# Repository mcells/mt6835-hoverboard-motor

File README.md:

# mt6835-hoverboard-motor
MT6835 Breakout board, eg. for mounting inside Hoverboard motors

| Front | Back |
| ----- | ---- | 
|  |  |

## Features
- MT6835 Encoder
- 25x25mm diagonal M3 mounting holes that are removable by breakaway sections
- 14.2mm diameter, making it small enough to fit onto the 15mm shaft of Hoverboard motors
- M2 mounting holes, 10.6mm apart to facilitate mounting.
  - Nonconductive screws or spacers are necessary to prevent shorts!
  - Designed to be screwed into corresponding M2 holes drilled and tapped into the shaft, the cabling will go through the drilled-out center of the shaft.
  - A similar approach is described [here](https://community.simplefoc.com/t/a-project-in-mind-force-feedback-wheel/952/27)
- Breakaway drill template
  - drill out the motor shaft to 5mm and use the drill bit to locate the template on-center, then mark and drill the M2 holes
- All usable Pins broken out to three sensible 6-pin headers
  - SPI interface on 1.27mm header, with enough space to mount a 6-pin 1.25mm Molex Picoblade
  - UVW and ABZ (together with CAL and PWM pins) on 1mm Pitch headers (due to space constraints)
- TVS diode footprint can accept the one from the breakout board commonly available on Aliexpress
- Sleek design
## Renders
| Front | Back |
| ----- | ---- | 
|  |  |

## Installation inside a Hoverboard motor

Installing the sensor board inside a Hoverboard motor requires you to have access to the following tools:
- A Hoverboard motor and
- A sensor board (obviously...)
- A drill press (though using a hand drill might work, if you are careful)
- 5mm HSS drill
- 2mm HSS drill for marking the locating holes
- 1,6mm or 1,7mm HSS drill for the M2 threads
- M2 tap
- two M2 screws for mounting the sensor
- soldering stuff
- a saw or dremel to cut out the round part of the PCB

### Steps

| Step | Image | Description |
| ---- | ----- | ----------- |
|   1  |       | Disassemble the Motor, until you have just the bare Stator. Desolder and pull out all wires, so you can drill through the shaft.|
|   2  |  | Drill a 5mm Hole inside the top of the stator shaft. There is a centered "dimple" already in the shaft, which helps with centering the drill enormously. You want everything to be as concentric as possible, else you will get a periodic nonlinearity in the measured angle! You have to drill about 25mm until you break through to the hollow shaft. |
|   3  |  | Remove the drill bit from the drill and put it most of the way through the new hole, so that just protrudes at the top. Use the drill bit to locate the template PCB on the center of the shaft. | 
|   4  |  | Either use a center punch, or, using a M2 drill bit, pre drill two "dimples", so you can later locate with the smaller drill bit. When drilling the second dimple, use something like a small allen wrench in the first dimple to hold the template in place. |
|   5  |  | Drill the two holes with a 1.6mm or 1.7mm bit and tap the holes to M2. You can use a 1.7mm drill to ease the tapping, as the threads don´t need to support any significant load. Also refrain from tapping more than a few mm deep, as it is absolutely not neccesary and just increases the risk of your tap snapping off. |
|   6  |  | You can now mount the sensor. Take care to use either 3d printed isolators like I did, or use plastic washers. Else you **will short** the sensor out! I had to drill out the 5mm hole to 6mm to make my sensor wires fit. If you have thinner wires, 5mm might be enough for you. I replaced the original wiring with new one. |
|  7 (optional) |  | In these motors, the 3 phases are each wound using multiple strands of enamelled copper wire, some 3, 4, or even 5 in parallel. The phases are then connected in a star, or Y topology. I wanted to lower the kV as much as possible, so I unsoldered the strands and connected them in series for each of the three phases. This lowers the kV by the number of strands you serialize, in my case three. |
|  8   |   |  My motors have just enough space inside, so that the magnet can be mounted directly inside the rotor bell. I marked the center of the bell by pushing a 15mm HSS drill into the bearing (15mm inside diameter) and turning the bell. This leaves a perfectly centered dimple exactly where you want to mount the magnet. The aluminium there is about 2-3mm thick. Drilling about 1mm with a drill bit of the same diameter as your magnet lets you just glue the magnet there, without drilling from the outside. |

## Where to get the boards

I got my PCBs fabbed and assembled at JLC. You can use the provided KiCad project files to generate the required files.
You don´t have to get assembled boards directly, as I designed the PCBs so that you can desolder the components from the aliexpress board and solder them onto this PCB. This might be far cheaper for single quantities.

If you have any questions, feel free to just create an issue/discussion or ask me on Discord (@hollowedbethyname)

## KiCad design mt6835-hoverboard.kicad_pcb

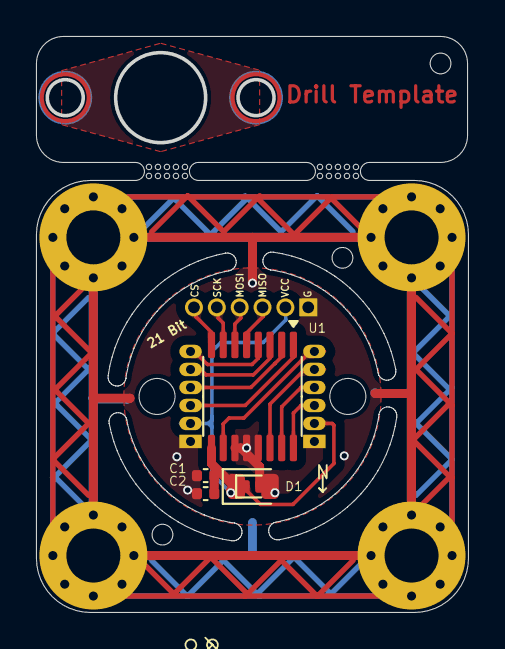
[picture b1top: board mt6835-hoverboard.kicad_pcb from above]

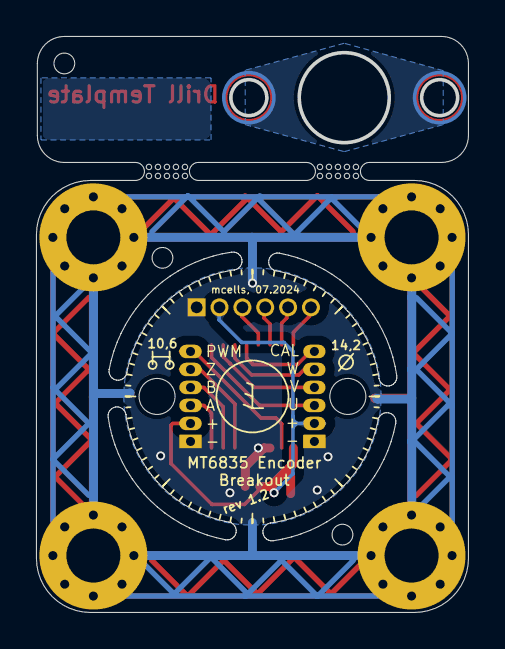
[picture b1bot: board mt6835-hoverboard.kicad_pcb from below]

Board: 2 copper layers, 23.9 x 31.9 mm, 7 parts (3 on the bottom side), 2 nets.

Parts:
C1, C2: 0.1µF; C_0402_1005Metric
D1: BDFN2A051U; D_SOD-882D
J1: PinHeader_1x06_P1.27mm_Vertical
J2, J3: PinHeader_1x06_P1.00mm_Vertical
U1: MT6835; TSSOP-16_4.4x5mm_P0.65mm

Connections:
GND: C1.1, C2.1, D1.2 (A2), J1.1, J2.1, J3.1, U1.11 (TEST), U1.12 (GND), U1.13 (TEST_EN)
unnamed: C1.2, C2.2, D1.1 (A1), J1.2, J2.2, J3.2, U1.9 (VDD)

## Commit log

2024-07-01 Add project files
2024-07-01 add images
2024-07-01 update schematic
2024-07-01 Add PDFs
2024-07-05 Make DRC happy, Add 25x25mm mounting and drill guide
2024-07-06 Add finishing touches to PCB
2024-07-08 Revision 1.1: Good for production
2024-07-21 Add Photos
2024-07-21 Add step by step instructions for modifying a motor
2024-07-21 add more images
2024-07-21 Add final step by step images
2024-07-21 Update Guide
2024-07-21 add isolator stls
2024-07-22 Add more info
2025-01-29 Rev 1.2: Move pinout silkscreen slightly
